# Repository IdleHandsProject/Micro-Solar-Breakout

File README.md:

# Micro-Solar-Breakout
Two small breakout boards for IXYS small solar cells.

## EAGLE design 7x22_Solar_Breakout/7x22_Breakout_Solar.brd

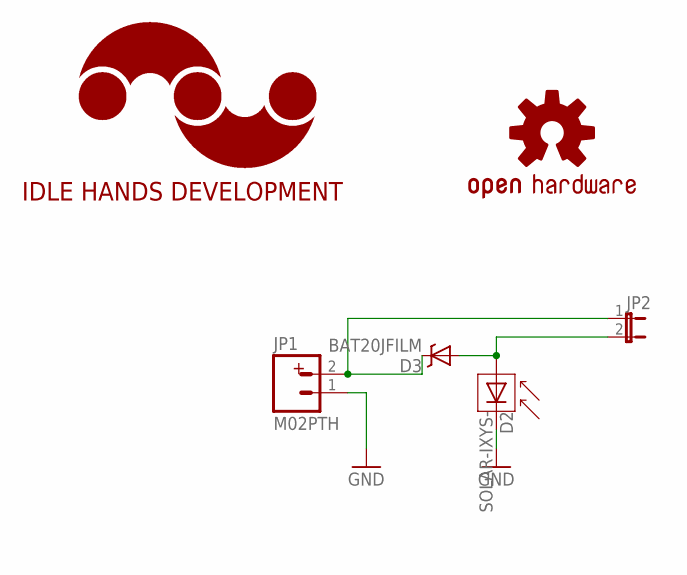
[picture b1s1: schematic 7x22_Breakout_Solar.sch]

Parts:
D2: SOLAR-IXYS-; SOLARBIT-12X1
D3: BAT20JFILM; SOD-323
JP1: M02PTH; 1X02
JP2: JUMPER-2SMD-NO; SJ_2S-NO
LOGO1: IDLEHANDS_LOGOS; IHD-LOGO-S
LOGO2: OSHW-LOGOS; OSHW-LOGO-S

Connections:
GND: D2.- (C), JP1.1
INC: D2.+ (A), D3.2 (A), JP2.2
INO: D3.1 (C), JP1.2, JP2.1

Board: 2 copper layers, 6 parts (2 on the bottom side), 3 nets, no tracks yet.

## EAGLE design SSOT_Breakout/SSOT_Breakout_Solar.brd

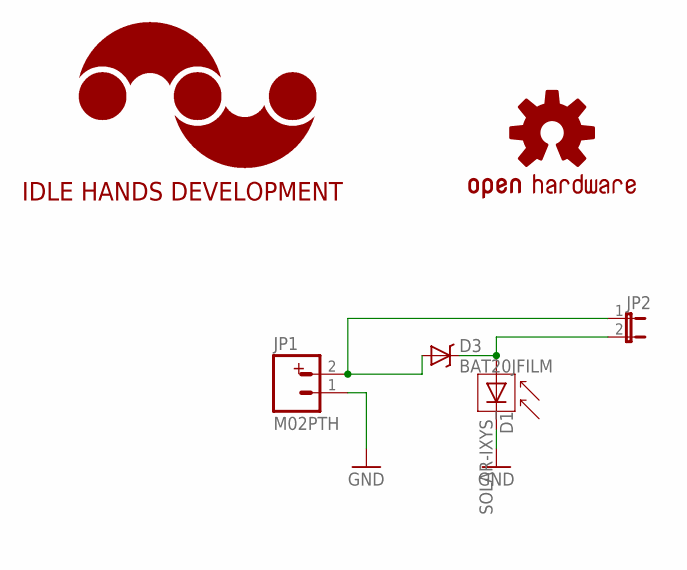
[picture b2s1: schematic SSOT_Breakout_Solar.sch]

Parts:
D1: SOLAR-IXYS_; SO08
D3: BAT20JFILM; SOD-323
JP1: M02PTH; 1X02
JP2: JUMPER-2SMD-NO; SJ_2S-NO
LOGO1: IDLEHANDS_LOGOS; IHD-LOGO-S
LOGO2: OSHW-LOGOS; OSHW-LOGO-S

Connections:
GND: D1.5 (C), JP1.1
INC: D1.8 (A), D3.1 (C), JP2.2
INO: D3.2 (A), JP1.2, JP2.1

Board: 2 copper layers, 6 parts (2 on the bottom side), 3 nets, no tracks yet.

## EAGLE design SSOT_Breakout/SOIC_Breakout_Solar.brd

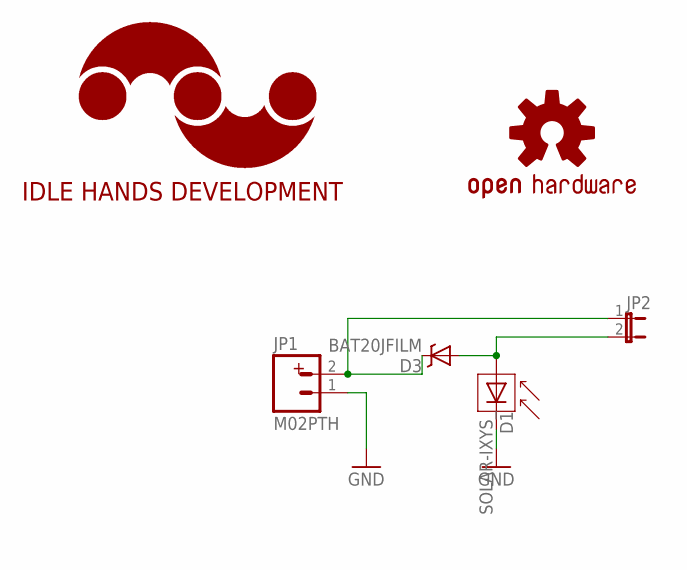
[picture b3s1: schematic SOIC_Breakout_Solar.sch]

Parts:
D1: SOLAR-IXYS_; SO08
D3: BAT20JFILM; SOD-323
JP1: M02PTH; 1X02
JP2: JUMPER-2SMD-NO; SJ_2S-NO
LOGO1: IDLEHANDS_LOGOS; IHD-LOGO-S
LOGO2: OSHW-LOGOS; OSHW-LOGO-S

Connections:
GND: D1.5 (C), JP1.1
INC: D1.8 (A), D3.2 (A), JP2.2
INO: D3.1 (C), JP1.2, JP2.1

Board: 2 copper layers, 6 parts (2 on the bottom side), 3 nets, no tracks yet.

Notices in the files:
parts and their libraries:
SparkFun-Sensors: Licensing: CC v3.0 Share-Alike You are welcome to use this library for commercial purposes.
